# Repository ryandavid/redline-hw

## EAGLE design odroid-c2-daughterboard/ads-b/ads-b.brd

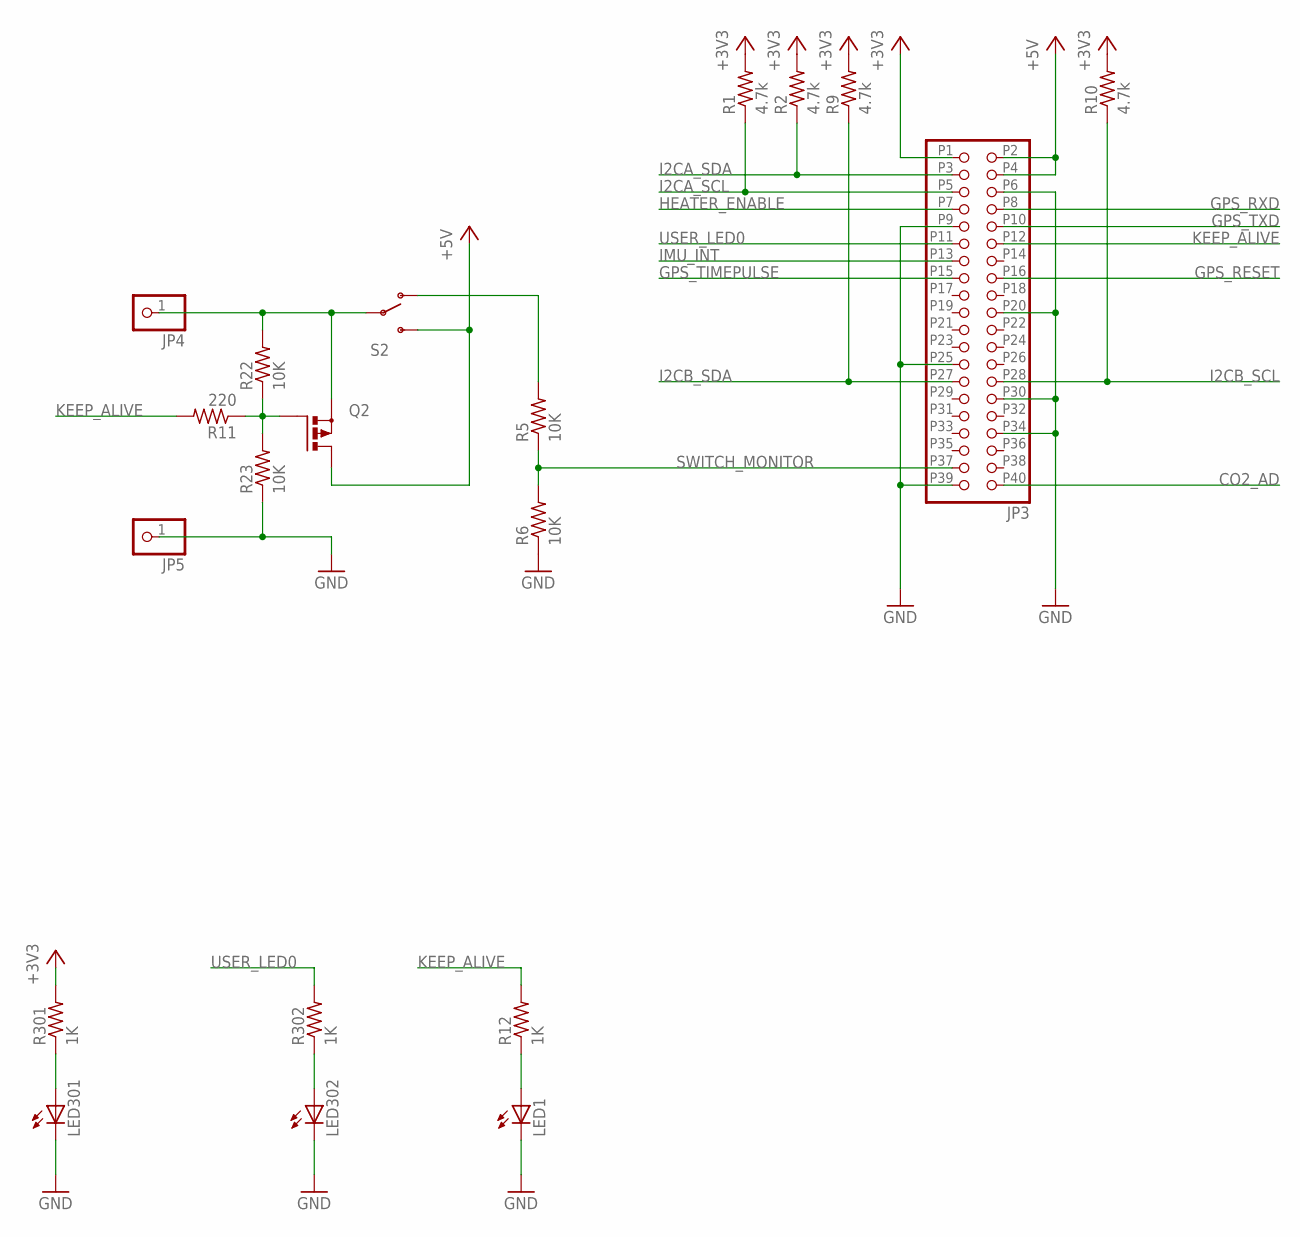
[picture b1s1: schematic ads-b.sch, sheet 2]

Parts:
JP3: ODROID-C2; 2X20
JP4, JP5: PINHD-1X1; 1X01
LED1, LED301, LED302: LEDSML0603; SML0603
Q2: P-MOSFET-SO8; SO-08
R1, R2, R9, R10: 4.7k; R0603
R5, R6, R22, R23: 10K; R0603
R11: 220; R0603
R12, R301, R302: 1K; R0603
S2: SWITCH-SPDTSMD2; SWITCH-SPDT-SMD

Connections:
+3V3: JP3.P1 (40), R1.2, R2.2, R9.2, R10.2, R301.2; also elsewhere on the board
+5V: JP3.P2 (39), JP3.P4 (37), Q2.5 (D), Q2.6 (D), Q2.7 (D), Q2.8 (D), S2.3 (S); also elsewhere on the board
CO2_AD: JP3.P40 (1); also elsewhere on the board
GND: JP3.P6 (35), JP3.P9 (32), JP3.P20 (21), JP3.P25 (16), JP3.P30 (11), JP3.P34 (7), JP3.P39 (2), JP5.1, LED1.C, LED301.C, LED302.C, R6.1, R23.1; also elsewhere on the board
GPS_RESET: JP3.P16 (25); also elsewhere on the board
GPS_RXD: JP3.P8 (33); also elsewhere on the board
GPS_TIMEPULSE: JP3.P15 (26); also elsewhere on the board
GPS_TXD: JP3.P10 (31); also elsewhere on the board
HEATER_ENABLE: JP3.P7 (34); also elsewhere on the board
I2CA_SCL: JP3.P5 (36), R1.1; also elsewhere on the board
I2CA_SDA: JP3.P3 (38), R2.1; also elsewhere on the board
I2CB_SCL: JP3.P28 (13), R10.1; also elsewhere on the board
I2CB_SDA: JP3.P27 (14), R9.1; also elsewhere on the board
IMU_INT: JP3.P13 (28); also elsewhere on the board
KEEP_ALIVE: JP3.P12 (29), R11.2, R12.2
unnamed: JP4.1, Q2.1 (S), Q2.2 (S), Q2.3 (S), R22.2, S2.2
unnamed: Q2.4 (G), R11.1, R22.1, R23.2
unnamed: R5.2, S2.1 (O)
SWITCH_MONITOR: JP3.P37 (4), R5.1, R6.2
USER_LED0: JP3.P11 (30), R302.2
VDD_PGOOD1: LED301.A, R301.1
VDD_PGOOD2: LED302.A, R302.1
VDD_PGOOD3: LED1.A, R12.1

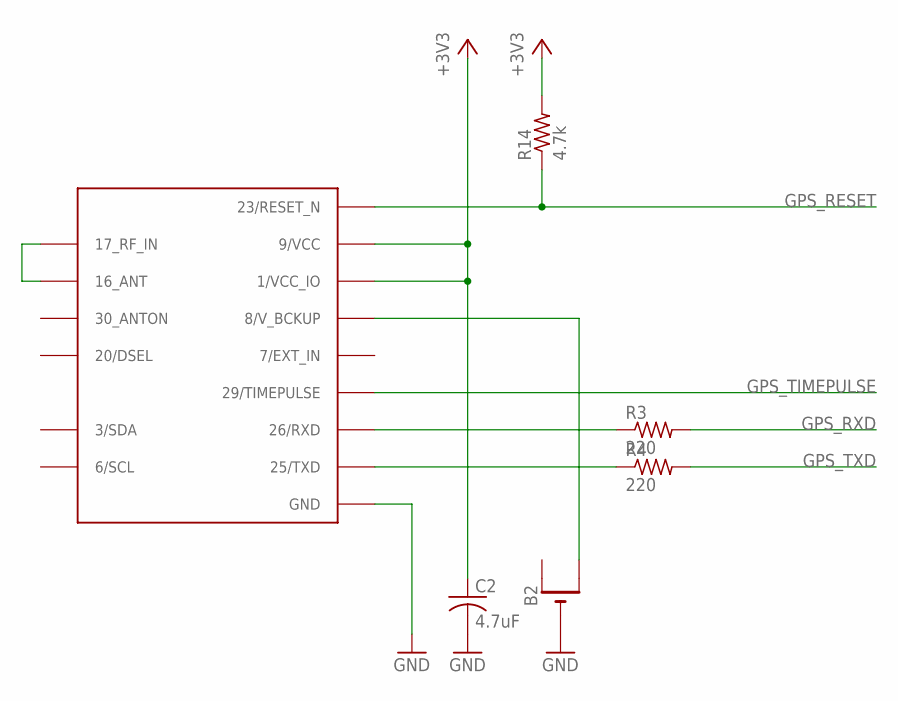
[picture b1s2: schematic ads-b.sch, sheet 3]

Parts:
B2: CR1220THM; CR1220-THM
C2: 4.7uF; C0603
R3, R4: 220; R0603
R14: 4.7k; R0603
U$2: UBLOX_CAM

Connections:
+3V3: C2.1, R14.2, U$2.1/VCC_IO, U$2.9/VCC; also elsewhere on the board
GND: B2.-, C2.2, U$2.4/GND (GND), U$2.5/GND (GND), U$2.10/GND (GND), U$2.11/GND (GND), U$2.12/GND (GND), U$2.13/GND (GND), U$2.14/GND (GND), U$2.15/GND (GND), U$2.18/GND (GND), U$2.19/GND (GND), U$2.21/GND (GND), U$2.22/GND (GND), U$2.27/GND (GND), U$2.31/GND (GND); also elsewhere on the board
GPS_RESET: R14.1, U$2.23/RESET_N; also elsewhere on the board
GPS_RXD: R3.2; also elsewhere on the board
GPS_TIMEPULSE: U$2.29/TIMEPULSE; also elsewhere on the board
GPS_TXD: R4.2; also elsewhere on the board
unnamed: B2.+2 (+1), U$2.8/V_BCKP (8/V_BCKUP)
unnamed: R3.1, U$2.26/RXD
unnamed: R4.1, U$2.25/TXD
unnamed: U$2.16/ANT (16_ANT), U$2.17/RF_IN (17_RF_IN)

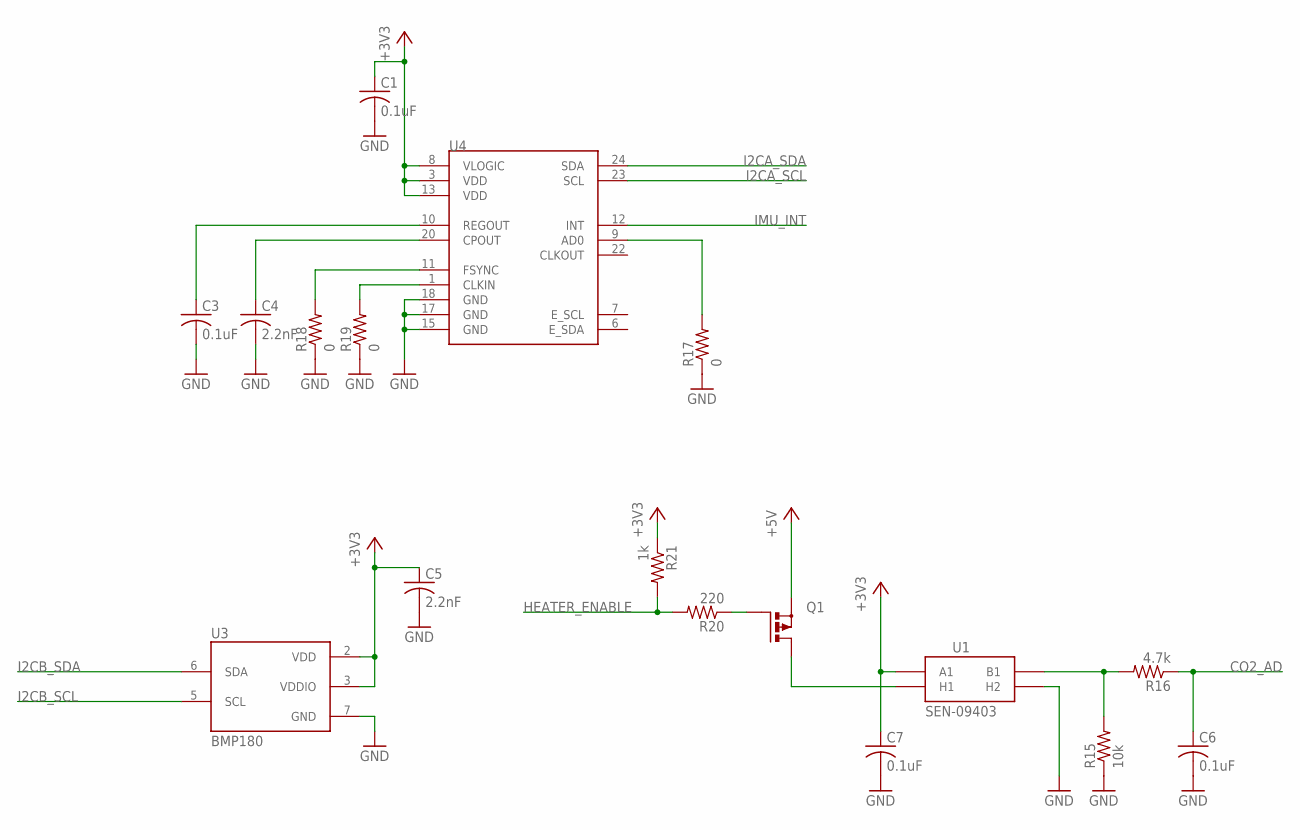
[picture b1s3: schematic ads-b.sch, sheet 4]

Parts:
C1, C3, C6, C7: 0.1uF; C0603
C4, C5: 2.2nF; C0603
Q1: P-MOSFET-SO8; SO-08
R15: 10k; R0603
R16: 4.7k; R0603
R17, R18, R19: 0; R0603
R20: 220; R0603
R21: 1k; R0603
U1: SEN-09403; MQ-3
U3: BMP180
U4: MPU-9150QFN-24-NP; QFN-24-NP

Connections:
+3V3: C1.1, C5.1, C7.1, R21.1, U1.A1, U3.2 (VDD), U3.3 (VDDIO), U4.3 (VDD), U4.8 (VLOGIC), U4.13 (VDD); also elsewhere on the board
+5V: Q1.1 (S), Q1.2 (S), Q1.3 (S); also elsewhere on the board
CO2_AD: C6.1, R16.1; also elsewhere on the board
GND: C1.2, C3.2, C4.2, C5.2, C6.2, C7.2, R15.1, R17.1, R18.1, R19.1, U1.HB (H2), U3.7 (GND), U4.15 (GND), U4.17 (GND), U4.18 (GND); also elsewhere on the board
HEATER_ENABLE: R20.2, R21.2; also elsewhere on the board
I2CA_SCL: U4.23 (SCL); also elsewhere on the board
I2CA_SDA: U4.24 (SDA); also elsewhere on the board
I2CB_SCL: U3.5 (SCL); also elsewhere on the board
I2CB_SDA: U3.6 (SDA); also elsewhere on the board
IMU_INT: U4.12 (INT); also elsewhere on the board
unnamed: C3.1, U4.10 (REGOUT)
unnamed: R15.2, R16.2, U1.B1
unnamed: C4.1, U4.20 (CPOUT)
unnamed: R17.2, U4.9 (AD0)
unnamed: R18.2, U4.11 (FSYNC)
unnamed: R19.2, U4.1 (CLKIN)
unnamed: Q1.5 (D), Q1.6 (D), Q1.7 (D), Q1.8 (D), U1.HA (H1)
unnamed: Q1.4 (G), R20.1

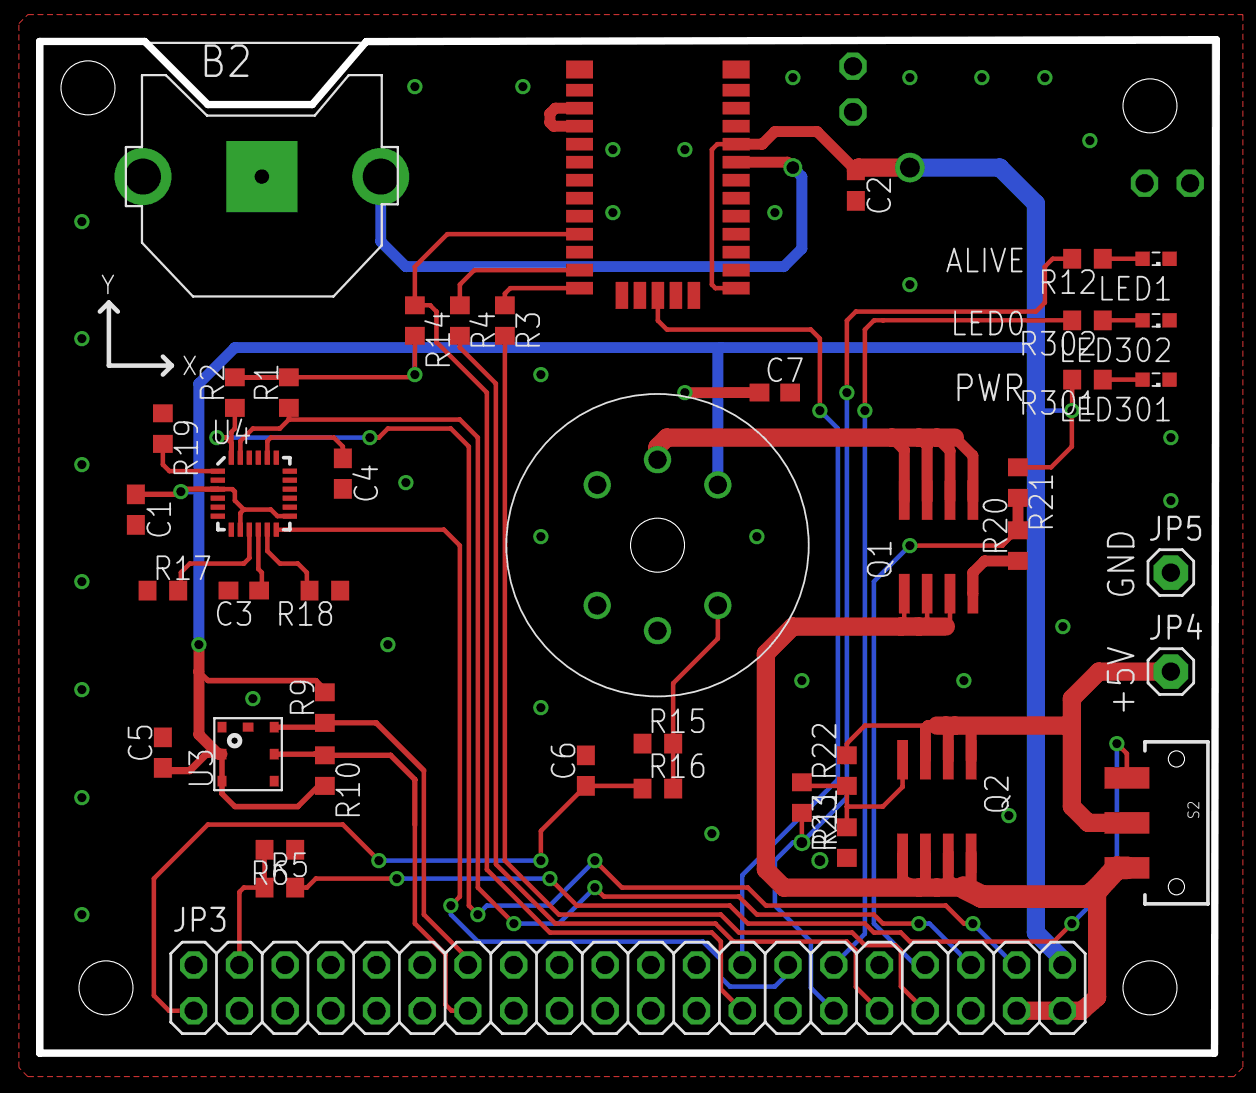
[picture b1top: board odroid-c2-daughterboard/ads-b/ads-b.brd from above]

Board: 2 copper layers, 65.4 x 56.3 mm, 43 parts (0 on the bottom side), 35 nets.

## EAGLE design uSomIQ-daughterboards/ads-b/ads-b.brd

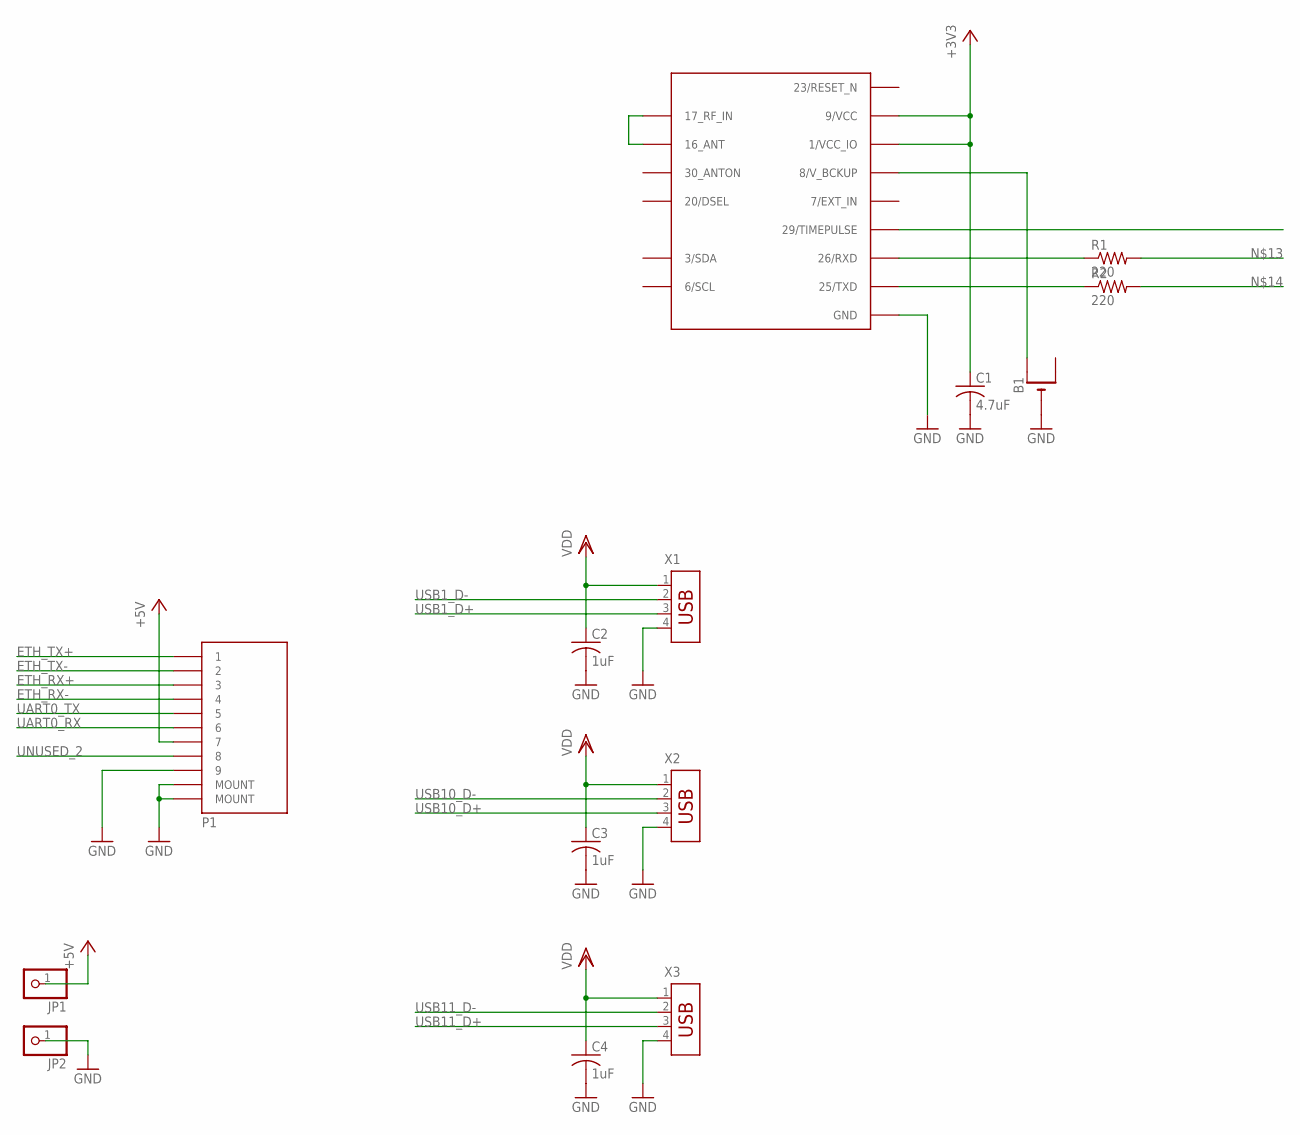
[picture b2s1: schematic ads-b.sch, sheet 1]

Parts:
B1: CR1220THM; CR1220-THM
C1: 4.7uF; C0603
C2, C3, C4: 1uF; C0603
JP1, JP2: PINHD-1X1; 1X01
P1: 83611-9006
R1, R2: 220; R0603
U$1: UBLOX_CAM
X1, X2, X3: USB-787616; USB

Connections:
23/RESET_N: U$1.23/RESET_N
+3V3: C1.1, U$1.1/VCC_IO, U$1.9/VCC; also elsewhere on the board
+5V: JP1.1, P1.7; also elsewhere on the board
ETH_RX+: P1.3; also elsewhere on the board
ETH_RX-: P1.4; also elsewhere on the board
ETH_TX+: P1.1; also elsewhere on the board
ETH_TX-: P1.2; also elsewhere on the board
GND: B1.-, C1.2, C2.2, C3.2, C4.2, JP2.1, P1.9, P1.MOUNT@1 (MOUNT), P1.MOUNT@2 (MOUNT), U$1.4/GND (GND), U$1.5/GND (GND), U$1.10/GND (GND), U$1.11/GND (GND), U$1.12/GND (GND), U$1.13/GND (GND), U$1.14/GND (GND), U$1.15/GND (GND), U$1.18/GND (GND), U$1.19/GND (GND), U$1.21/GND (GND), U$1.22/GND (GND), U$1.27/GND (GND), U$1.31/GND (GND), X1.4, X2.4, X3.4; also elsewhere on the board
unnamed: B1.+1 (+), U$1.8/V_BCKP (8/V_BCKUP)
unnamed: R1.1, U$1.26/RXD
unnamed: R2.1, U$1.25/TXD
unnamed: U$1.16/ANT (16_ANT), U$1.17/RF_IN (17_RF_IN)
UART0_RX: P1.6; also elsewhere on the board
UART0_TX: P1.5; also elsewhere on the board
UNUSED_2: P1.8
USB1_D+: X1.3; also elsewhere on the board
USB1_D-: X1.2; also elsewhere on the board
USB10_D+: X2.3; also elsewhere on the board
USB10_D-: X2.2; also elsewhere on the board
USB11_D+: X3.3; also elsewhere on the board
USB11_D-: X3.2; also elsewhere on the board
VDD: C2.1, C3.1, C4.1, X1.1, X2.1, X3.1; also elsewhere on the board

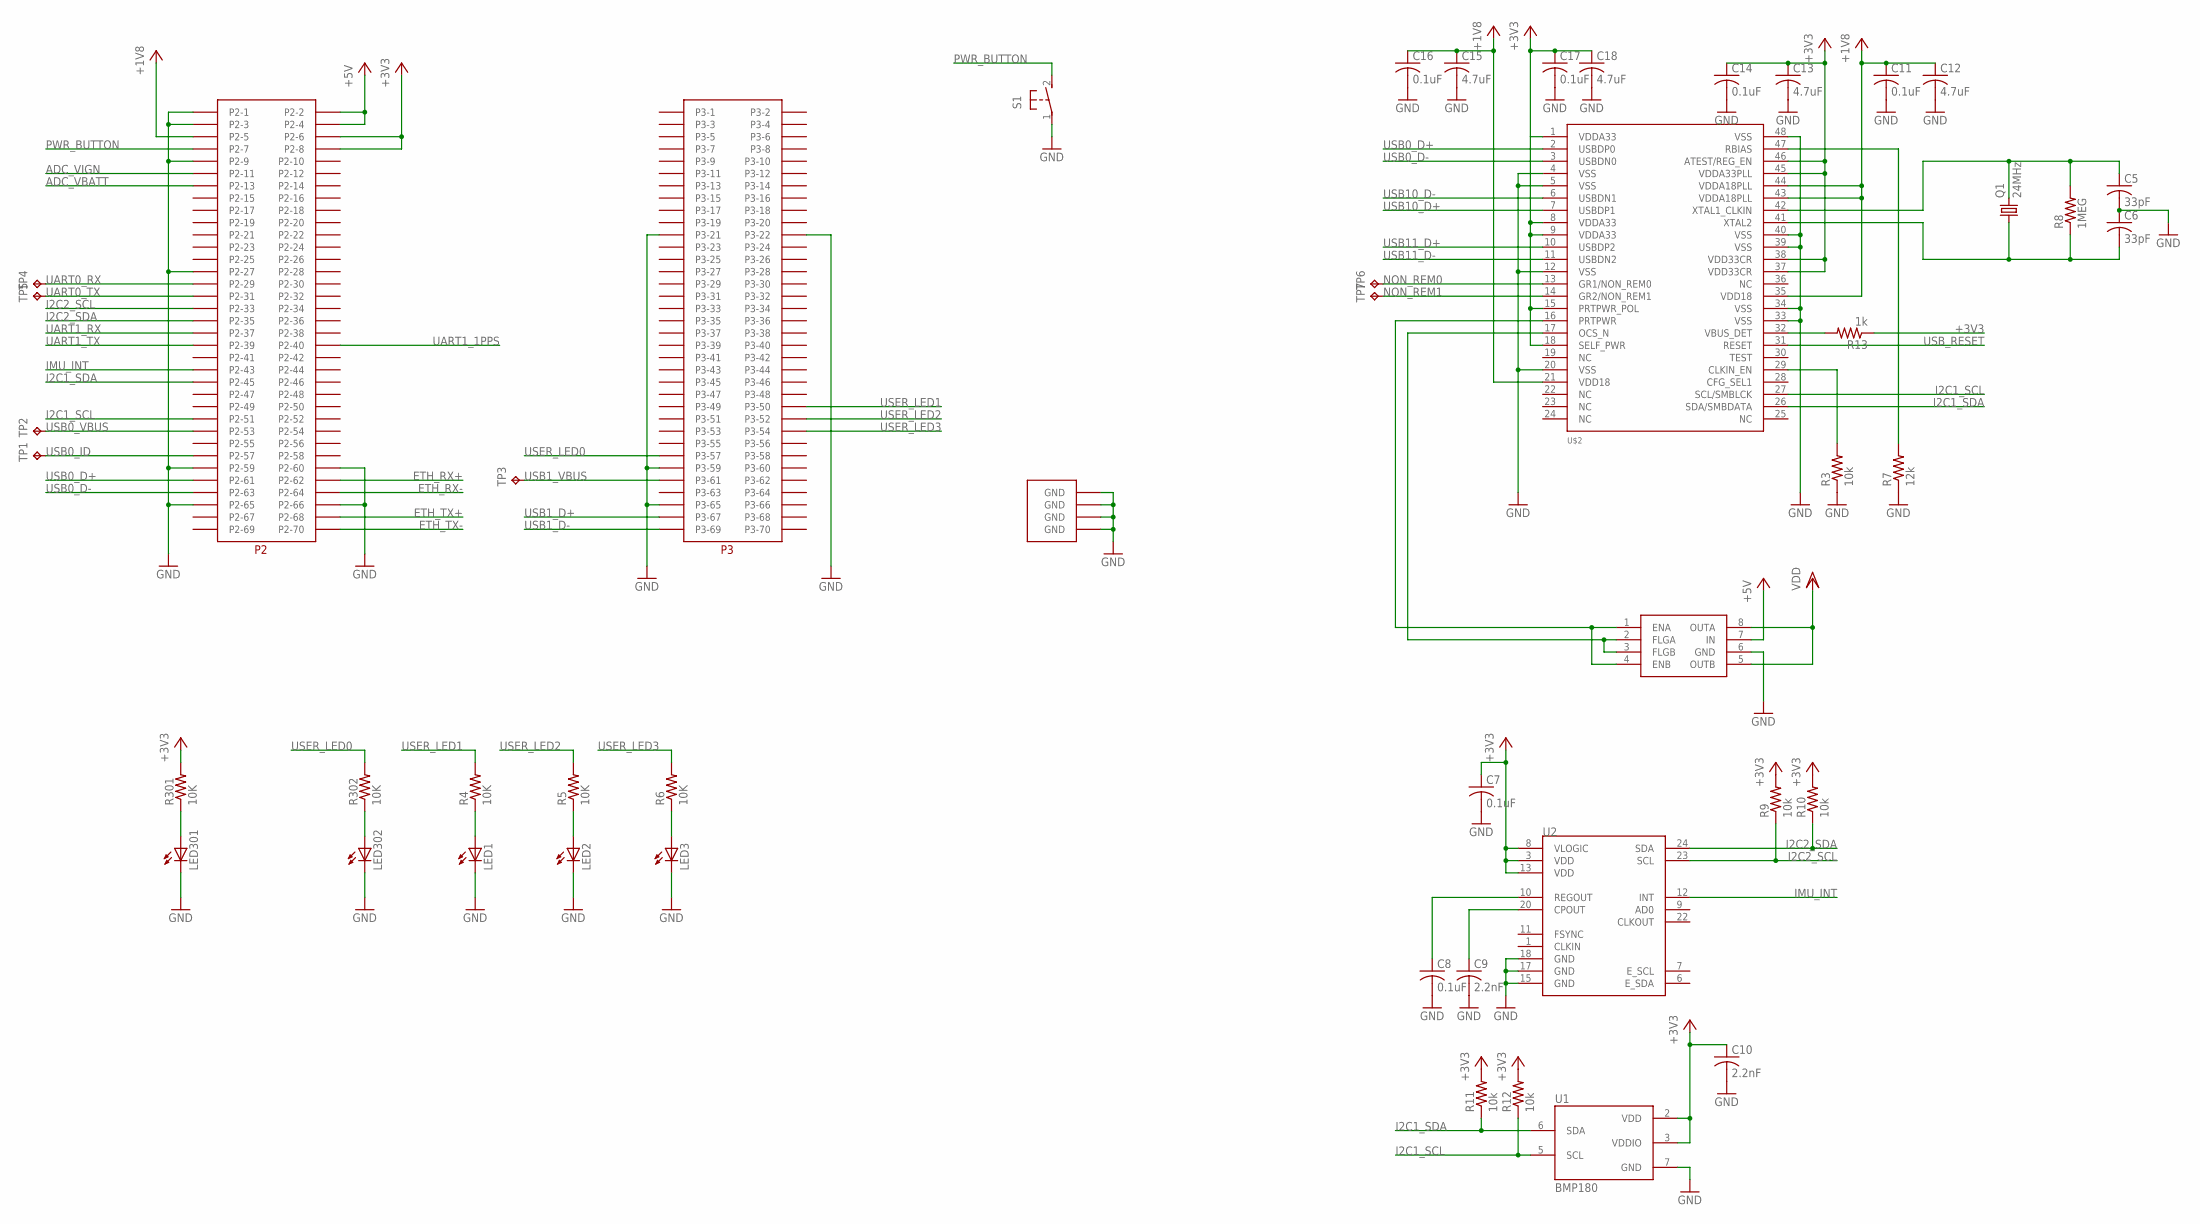
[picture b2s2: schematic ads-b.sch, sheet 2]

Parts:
C5, C6: 33pF; C0603
C7, C8, C11, C14, C16, C17: 0.1uF; C0603
C9, C10: 2.2nF; C0603
C12, C13, C15, C18: 4.7uF; C0603
LED1, LED2, LED3, LED301, LED302: LEDSML0603; SML0603
P301: USOMIQ-AM335X
Q1: 24MHz; HC49/S
R3, R9, R10, R11, R12: 10k; R0603
R4, R5, R6, R301, R302: 10K; R0603
R7: 12k; R0603
R8: 1MEG; R0603
R13: 1k; R0603
S1: 31-XX; B3F-31XX
TP1, TP2, TP3, TP4, TP5, TP6, TP7: TPB1,27; B1,27
U1: BMP180
U2: MPU-9150QFN-24-NP; QFN-24-NP
U$2: USB2502; S-PQFP-G48
U$3: MIC2026; SO8

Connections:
+3V3: C7.1, C10.1, C11.1, C12.1, C13.1, C14.1, C15.1, C16.1, C17.1, C18.1, P301.P$5 (P2-5), P301.P$6 (P2-6), P301.P$8 (P2-8), R9.2, R10.2, R11.2, R12.2, R13.1, R301.2, U1.2 (VDD), U1.3 (VDDIO), U2.3 (VDD), U2.8 (VLOGIC), U2.13 (VDD), U$2.1 (VDDA33), U$2.8 (VDDA33), U$2.9 (VDDA33), U$2.15 (PRTPWR_POL), U$2.18 (SELF_PWR), U$2.21 (VDD18), U$2.35 (VDD18), U$2.37 (VDD33CR), U$2.38 (VDD33CR), U$2.43 (VDDA18PLL), U$2.44 (VDDA18PLL), U$2.45 (VDDA33PLL), U$2.46 (ATEST/REG_EN); also elsewhere on the board
+5V: P301.P$2 (P2-2), P301.P$4 (P2-4), U$3.7 (IN); also elsewhere on the board
ADC_VBATT: P301.P$13 (P2-13)
ADC_VIGN: P301.P$11 (P2-11)
ETH_RX+: P301.P$62 (P2-62); also elsewhere on the board
ETH_RX-: P301.P$64 (P2-64); also elsewhere on the board
ETH_TX+: P301.P$68 (P2-68); also elsewhere on the board
ETH_TX-: P301.P$70 (P2-70); also elsewhere on the board
GND: C5.2, C6.1, C7.2, C8.2, C9.2, C10.2, C11.2, C12.2, C13.2, C14.2, C15.2, C16.2, C17.2, C18.2, LED1.C, LED2.C, LED3.C, LED301.C, LED302.C, P301.MOUNT@0 (GND), P301.MOUNT@1 (GND), P301.MOUNT@2 (GND), P301.MOUNT@3 (GND), P301.P$1 (P2-1), P301.P$3 (P2-3), P301.P$9 (P2-9), P301.P$27 (P2-27), P301.P$59 (P2-59), P301.P$60 (P2-60), P301.P$65 (P2-65), P301.P$66 (P2-66), P301.P$91 (P3-21), P301.P$92 (P3-22), P301.P$129 (P3-59), P301.P$135 (P3-65), R3.1, R7.1, S1.1, U1.7 (GND), U2.15 (GND), U2.17 (GND), U2.18 (GND), U$2.4 (VSS), U$2.5 (VSS), U$2.12 (VSS), U$2.20 (VSS), U$2.33 (VSS), U$2.34 (VSS), U$2.39 (VSS), U$2.40 (VSS), U$2.48 (VSS), U$3.6 (GND); also elsewhere on the board
I2C1_SCL: P301.P$51 (P2-51), R12.1, U1.5 (SCL), U$2.27 (SCL/SMBLCK)
I2C1_SDA: P301.P$45 (P2-45), R11.1, U1.6 (SDA), U$2.26 (SDA/SMBDATA)
I2C2_SCL: P301.P$33 (P2-33), R9.1, U2.23 (SCL)
I2C2_SDA: P301.P$35 (P2-35), R10.1, U2.24 (SDA)
IMU_INT: P301.P$43 (P2-43), U2.12 (INT)
unnamed: R3.2, U$2.29 (CLKIN_EN)
unnamed: U$2.16 (PRTPWR), U$3.1 (ENA), U$3.4 (ENB)
unnamed: R7.2, U$2.47 (RBIAS)
unnamed: C5.1, Q1.2, R8.2, U$2.42 (XTAL1_CLKIN)
unnamed: C6.2, Q1.1, R8.1, U$2.41 (XTAL2)
unnamed: C8.1, U2.10 (REGOUT)
unnamed: C9.1, U2.20 (CPOUT)
unnamed: U$2.17 (OCS_N), U$3.2 (FLGA), U$3.3 (FLGB)
unnamed: R13.2, U$2.32 (VBUS_DET)
NON_REM0: TP6.TP, U$2.13 (GR1/NON_REM0)
NON_REM1: TP7.TP, U$2.14 (GR2/NON_REM1)
PWR_BUTTON: P301.P$7 (P2-7), S1.2 (S)
UART0_RX: P301.P$29 (P2-29), TP4.TP; also elsewhere on the board
UART0_TX: P301.P$31 (P2-31), TP5.TP; also elsewhere on the board
UART1_1PPS: P301.P$40 (P2-40)
UART1_RX: P301.P$37 (P2-37)
UART1_TX: P301.P$39 (P2-39)
USB0_D+: P301.P$61 (P2-61), U$2.2 (USBDP0)
USB0_D-: P301.P$63 (P2-63), U$2.3 (USBDN0)
USB0_ID: P301.P$57 (P2-57), TP1.TP
USB0_VBUS: P301.P$53 (P2-53), TP2.TP
USB1_D+: P301.P$137 (P3-67); also elsewhere on the board
USB1_D-: P301.P$139 (P3-69); also elsewhere on the board
USB1_VBUS: P301.P$131 (P3-61), TP3.TP
USB10_D+: U$2.7 (USBDP1); also elsewhere on the board
USB10_D-: U$2.6 (USBDN1); also elsewhere on the board
USB11_D+: U$2.10 (USBDP2); also elsewhere on the board
USB11_D-: U$2.11 (USBDN2); also elsewhere on the board
USB_RESET: U$2.31 (RESET)
USER_LED0: P301.P$127 (P3-57), R302.2
USER_LED1: P301.P$120 (P3-50), R4.2
USER_LED2: P301.P$122 (P3-52), R5.2
USER_LED3: P301.P$124 (P3-54), R6.2
VDD: U$3.5 (OUTB), U$3.8 (OUTA); also elsewhere on the board
VDD_PGOOD1: LED301.A, R301.1
VDD_PGOOD2: LED302.A, R302.1
VDD_PGOOD3: LED1.A, R4.1
VDD_PGOOD4: LED2.A, R5.1
VDD_PGOOD5: LED3.A, R6.1

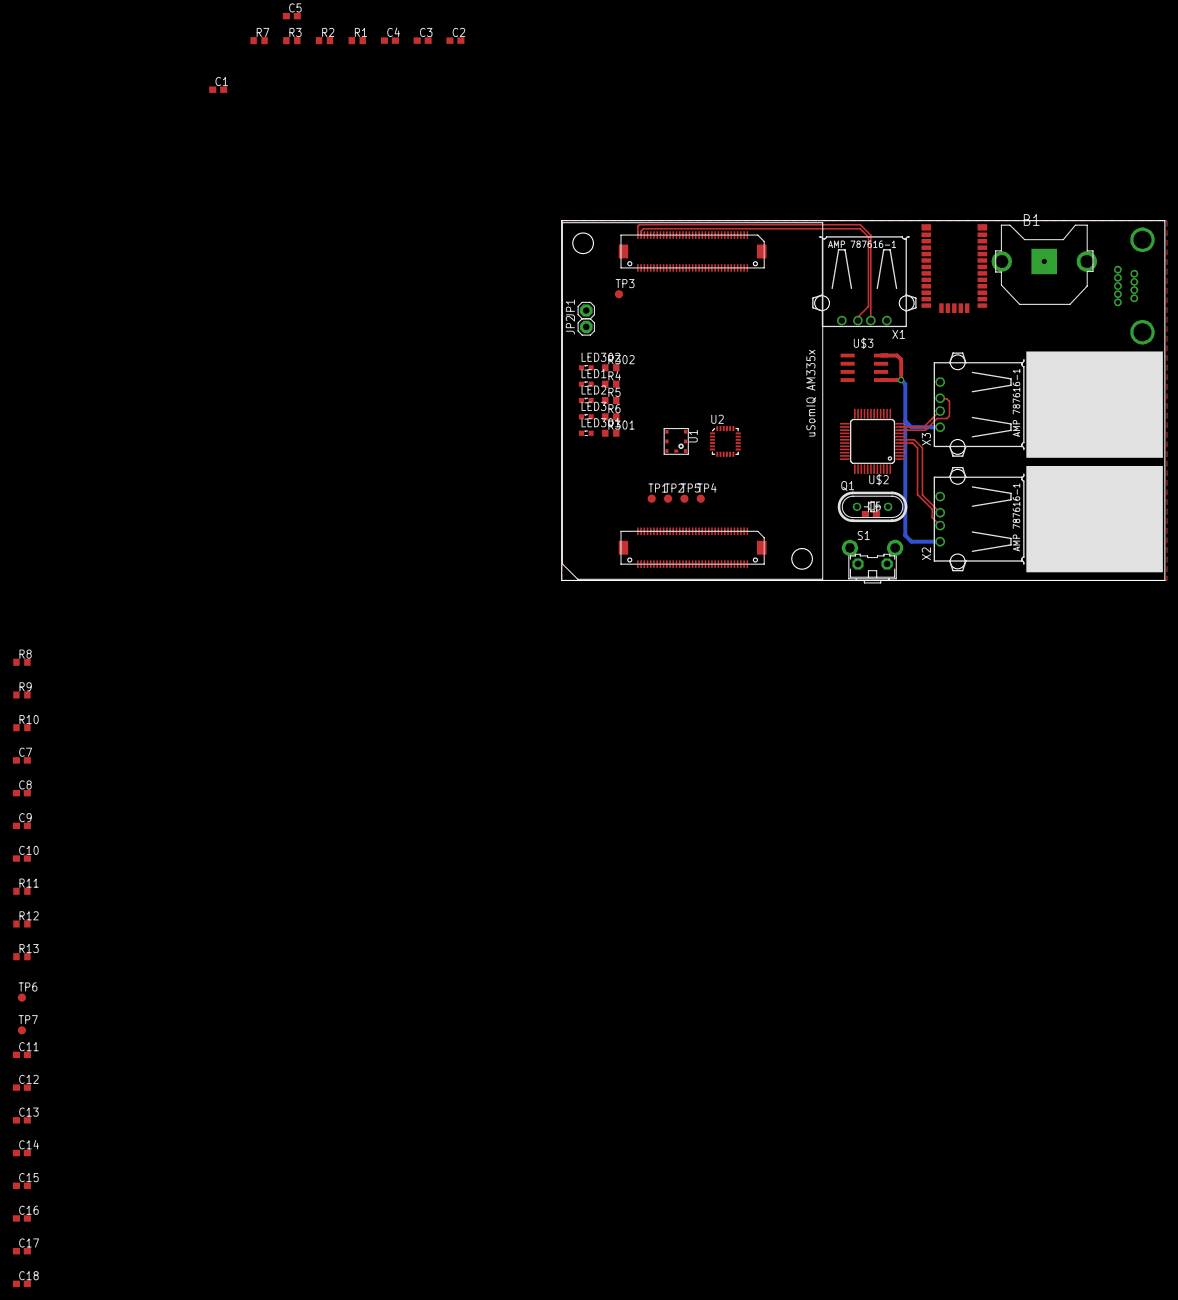
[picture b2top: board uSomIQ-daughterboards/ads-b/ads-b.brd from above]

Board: 2 copper layers, 93.7 x 55.9 mm, 60 parts (0 on the bottom side), 51 nets.

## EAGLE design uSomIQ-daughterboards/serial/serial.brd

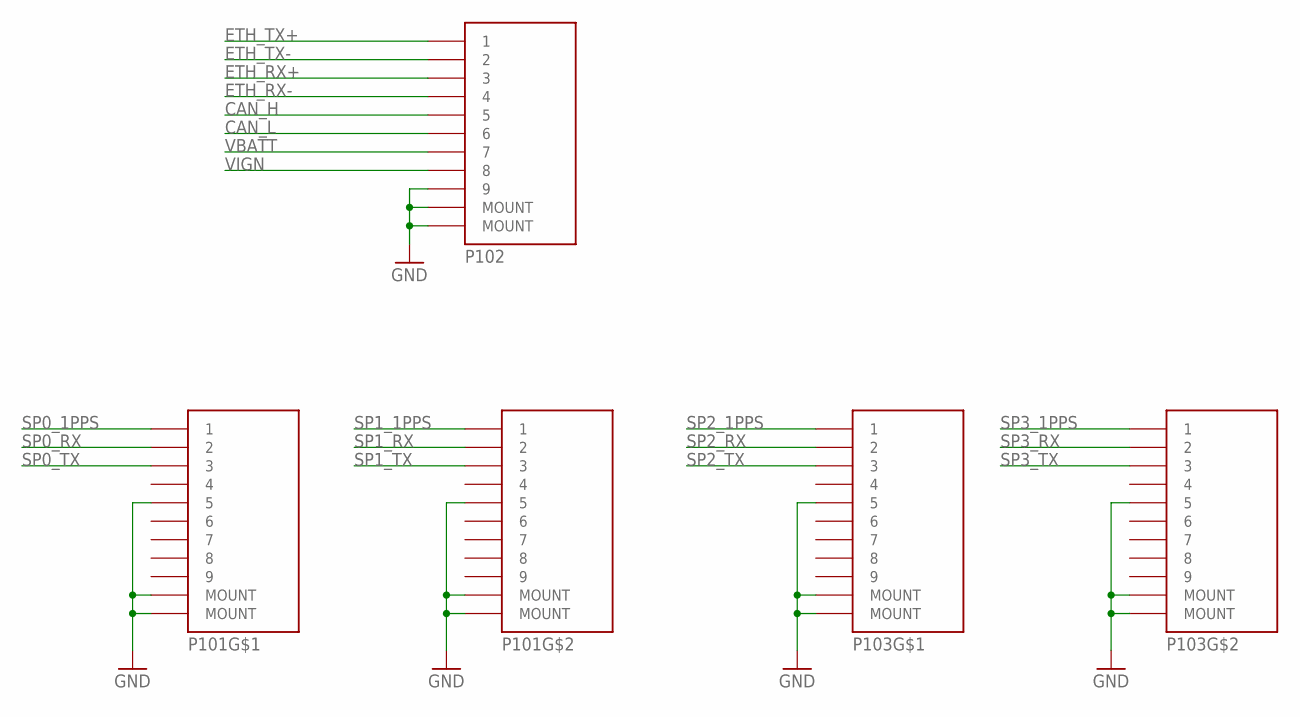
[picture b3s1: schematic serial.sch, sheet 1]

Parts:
P101, P103: 189-009-613R571
P102: 83611-9006

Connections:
CAN_H: P102.5
CAN_L: P102.6
ETH_RX+: P102.3; also elsewhere on the board
ETH_RX-: P102.4; also elsewhere on the board
ETH_TX+: P102.1; also elsewhere on the board
ETH_TX-: P102.2; also elsewhere on the board
GND: P101.A-5 (5), P101.B2 (5), P101.MOUNT@1 (MOUNT), P101.MOUNT@2 (MOUNT), P101.MOUNT@3 (MOUNT), P101.MOUNT@4 (MOUNT), P102.9, P102.MOUNT@1 (MOUNT), P102.MOUNT@2 (MOUNT), P103.A-5 (5), P103.B2 (5), P103.MOUNT@1 (MOUNT), P103.MOUNT@2 (MOUNT), P103.MOUNT@3 (MOUNT), P103.MOUNT@4 (MOUNT); also elsewhere on the board
SP0_1PPS: P101.A-1 (1); also elsewhere on the board
SP0_RX: P101.A-2 (2); also elsewhere on the board
SP0_TX: P101.A-3 (3); also elsewhere on the board
SP1_1PPS: P101.B-1 (1); also elsewhere on the board
SP1_RX: P101.B-3 (2); also elsewhere on the board
SP1_TX: P101.B-4 (3); also elsewhere on the board
SP2_1PPS: P103.A-1 (1); also elsewhere on the board
SP2_RX: P103.A-2 (2); also elsewhere on the board
SP2_TX: P103.A-3 (3); also elsewhere on the board
SP3_1PPS: P103.B-1 (1); also elsewhere on the board
SP3_RX: P103.B-3 (2); also elsewhere on the board
SP3_TX: P103.B-4 (3); also elsewhere on the board
VBATT: P102.7; also elsewhere on the board
VIGN: P102.8; also elsewhere on the board

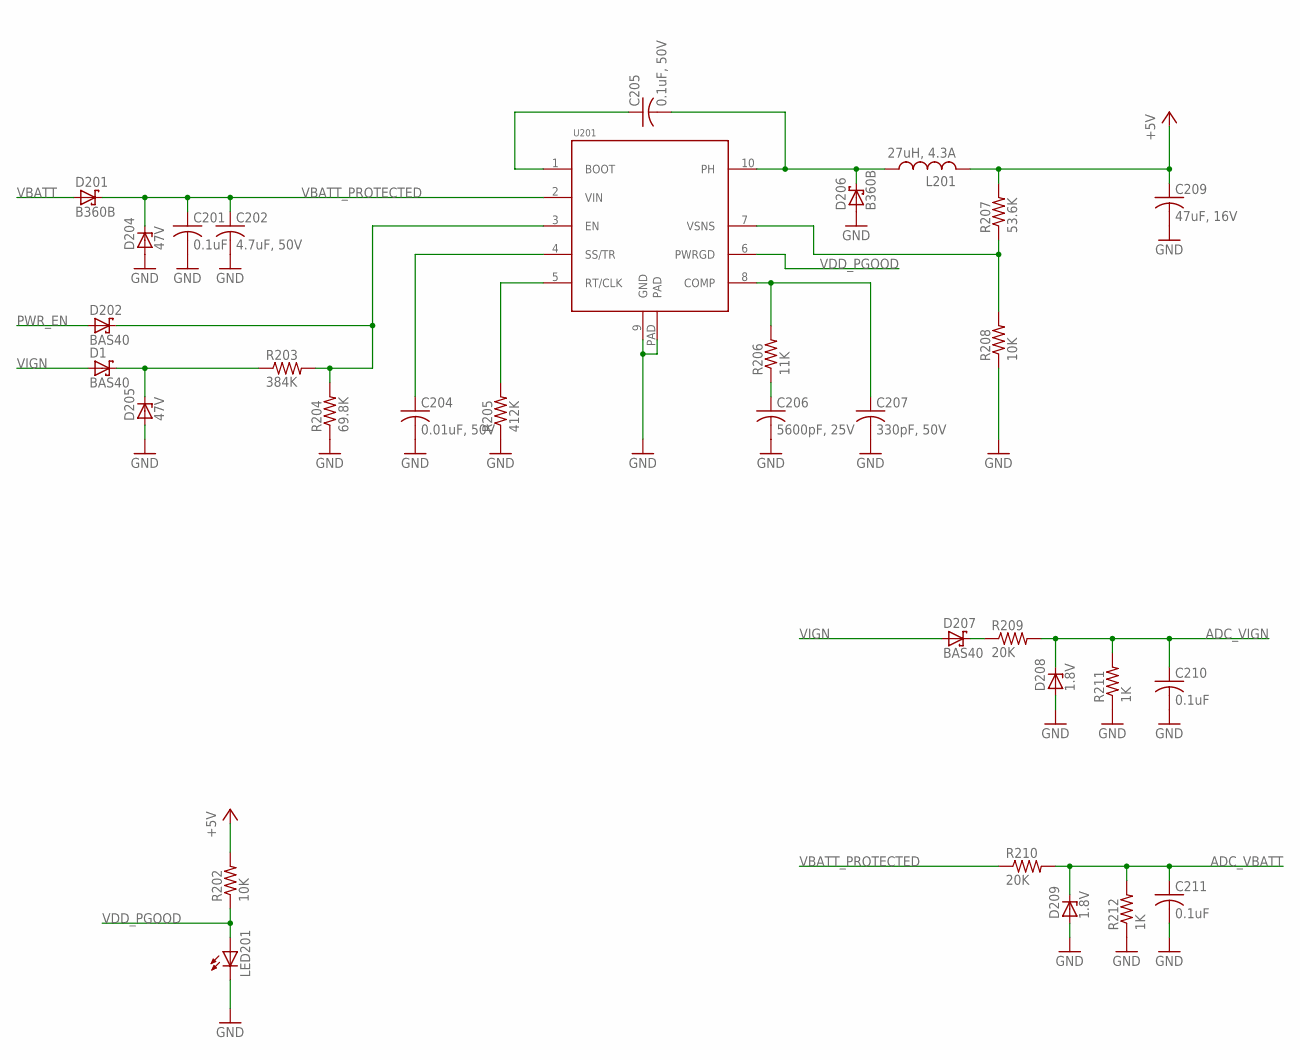
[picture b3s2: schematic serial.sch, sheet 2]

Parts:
C201: 0.1uF; C1210
C202: 4.7uF, 50V; C1210
C204: 0.01uF, 50V; C0603
C205: 0.1uF, 50V; C0603
C206: 5600pF, 25V; C0603
C207: 330pF, 50V; C0603
C209: 47uF, 16V; C2220K
C210, C211: 0.1uF; C0603
D1, D202, D207: BAS40; SOT23
D201, D206: B360B; SMB
D204: 47V; SMB
D205: 47V; SOT23
D208, D209: 1.8V; SOT23
L201: 27uH, 4.3A; 7447798271
LED201: LEDSML0603; SML0603
R202, R208: 10K; R0603
R203: 384K; R0603
R204: 69.8K; R0603
R205: 412K; R0603
R206: 11K; R0603
R207: 53.6K; R0603
R209, R210: 20K; R0603
R211, R212: 1K; R0603
U201: TPS54260; S-PDSO-G10

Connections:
+5V: C209.1, L201.P$2 (2), R202.2, R207.2; also elsewhere on the board
ADC_VBATT: C211.1, D209.3 (C), R210.2, R212.2; also elsewhere on the board
ADC_VIGN: C210.1, D208.3 (C), R209.2, R211.2; also elsewhere on the board
GND: C201.2, C202.2, C204.2, C206.2, C207.2, C209.2, C210.2, C211.2, D204.A, D205.1 (A), D206.A, D208.1 (A), D209.1 (A), LED201.C, R204.1, R205.1, R208.1, R211.1, R212.1, U201.9 (GND), U201.PAD; also elsewhere on the board
unnamed: C204.1, U201.4 (SS/TR)
unnamed: D1.3 (C), D205.3 (C), R203.1
unnamed: D202.3 (C), R203.2, R204.2, U201.3 (EN)
unnamed: R205.2, U201.5 (RT/CLK)
unnamed: C205.1, U201.1 (BOOT)
unnamed: C205.2, D206.C, L201.P$1 (1), U201.10 (PH)
unnamed: R207.1, R208.2, U201.7 (VSNS)
unnamed: C207.1, R206.2, U201.8 (COMP)
unnamed: C206.1, R206.1
unnamed: D207.3 (C), R209.1
PWR_EN: D202.1 (A); also elsewhere on the board
VBATT: D201.A; also elsewhere on the board
VBATT_PROTECTED: C201.1, C202.1, D201.C, D204.C, R210.1, U201.2 (VIN)
VDD_PGOOD: LED201.A, R202.1, U201.6 (PWRGD)
VIGN: D1.1 (A), D207.1 (A); also elsewhere on the board

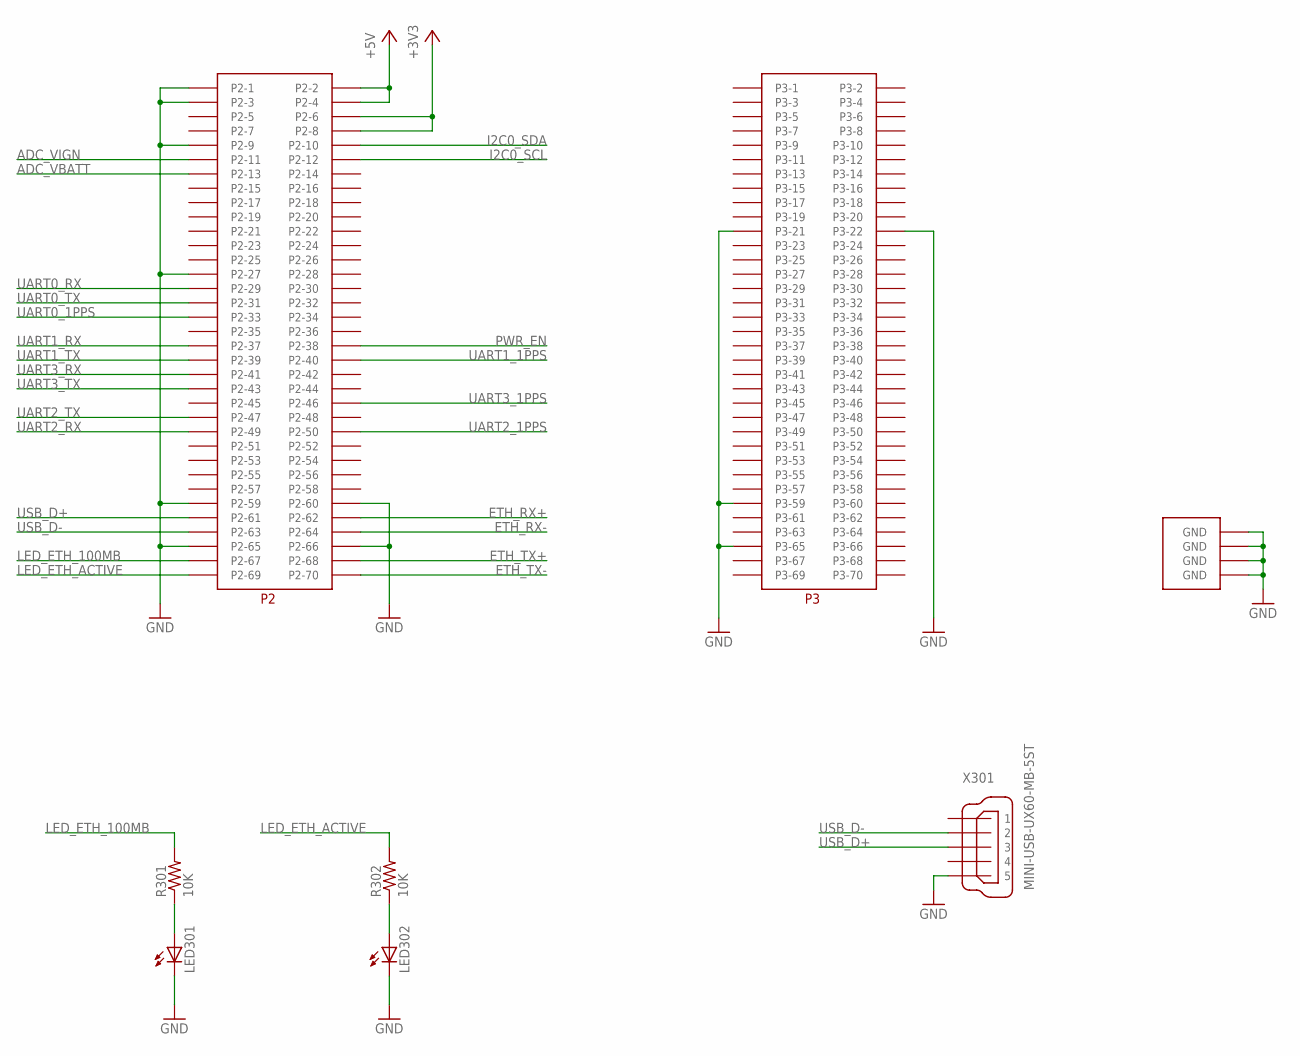
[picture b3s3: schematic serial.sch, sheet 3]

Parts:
LED301, LED302: LEDSML0603; SML0603
P301: USOMIQ-AM335X
R301, R302: 10K; R0603
X301: MINI-USB-UX60-MB-5ST; UX60-MB-5ST

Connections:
+3V3: P301.P$6 (P2-6), P301.P$8 (P2-8); also elsewhere on the board
+5V: P301.P$2 (P2-2), P301.P$4 (P2-4); also elsewhere on the board
ADC_VBATT: P301.P$13 (P2-13); also elsewhere on the board
ADC_VIGN: P301.P$11 (P2-11); also elsewhere on the board
ETH_RX+: P301.P$62 (P2-62); also elsewhere on the board
ETH_RX-: P301.P$64 (P2-64); also elsewhere on the board
ETH_TX+: P301.P$68 (P2-68); also elsewhere on the board
ETH_TX-: P301.P$70 (P2-70); also elsewhere on the board
GND: LED301.C, LED302.C, P301.MOUNT@0 (GND), P301.MOUNT@1 (GND), P301.MOUNT@2 (GND), P301.MOUNT@3 (GND), P301.P$1 (P2-1), P301.P$3 (P2-3), P301.P$9 (P2-9), P301.P$27 (P2-27), P301.P$59 (P2-59), P301.P$60 (P2-60), P301.P$65 (P2-65), P301.P$66 (P2-66), P301.P$91 (P3-21), P301.P$92 (P3-22), P301.P$129 (P3-59), P301.P$135 (P3-65), X301.5; also elsewhere on the board
I2C0_SCL: P301.P$12 (P2-12); also elsewhere on the board
I2C0_SDA: P301.P$10 (P2-10); also elsewhere on the board
LED_ETH_100MB: P301.P$67 (P2-67), R301.2
LED_ETH_ACTIVE: P301.P$69 (P2-69), R302.2
PWR_EN: P301.P$38 (P2-38); also elsewhere on the board
UART0_1PPS: P301.P$33 (P2-33); also elsewhere on the board
UART0_RX: P301.P$29 (P2-29); also elsewhere on the board
UART0_TX: P301.P$31 (P2-31); also elsewhere on the board
UART1_1PPS: P301.P$40 (P2-40); also elsewhere on the board
UART1_RX: P301.P$37 (P2-37); also elsewhere on the board
UART1_TX: P301.P$39 (P2-39); also elsewhere on the board
UART2_1PPS: P301.P$50 (P2-50); also elsewhere on the board
UART2_RX: P301.P$49 (P2-49); also elsewhere on the board
UART2_TX: P301.P$47 (P2-47); also elsewhere on the board
UART3_1PPS: P301.P$46 (P2-46); also elsewhere on the board
UART3_RX: P301.P$41 (P2-41); also elsewhere on the board
UART3_TX: P301.P$43 (P2-43); also elsewhere on the board
USB_D+: P301.P$61 (P2-61), X301.3
USB_D-: P301.P$63 (P2-63), X301.2
VDD_PGOOD1: LED301.A, R301.1
VDD_PGOOD2: LED302.A, R302.1

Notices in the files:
parts and their libraries:
SparkFun-Sensors: Licensing: Creative Commons ShareAlike 4.0 International - https://creativecommons.org/licenses/by-sa/4.0
